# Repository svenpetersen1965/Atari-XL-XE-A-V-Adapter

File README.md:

# Atari-XL-XE-A-V-Adapter
This is an A/V-Adapter for the Atari 8bit XL and XE. It provides a connector for S-Video, which will work with the XE models and with XL models, that have the S-Video mod.

The BOM value (13.11.2023) for the PCB and components is 10.87€. This does not include the 3D printed case or any shipping fees to be paid for the components.

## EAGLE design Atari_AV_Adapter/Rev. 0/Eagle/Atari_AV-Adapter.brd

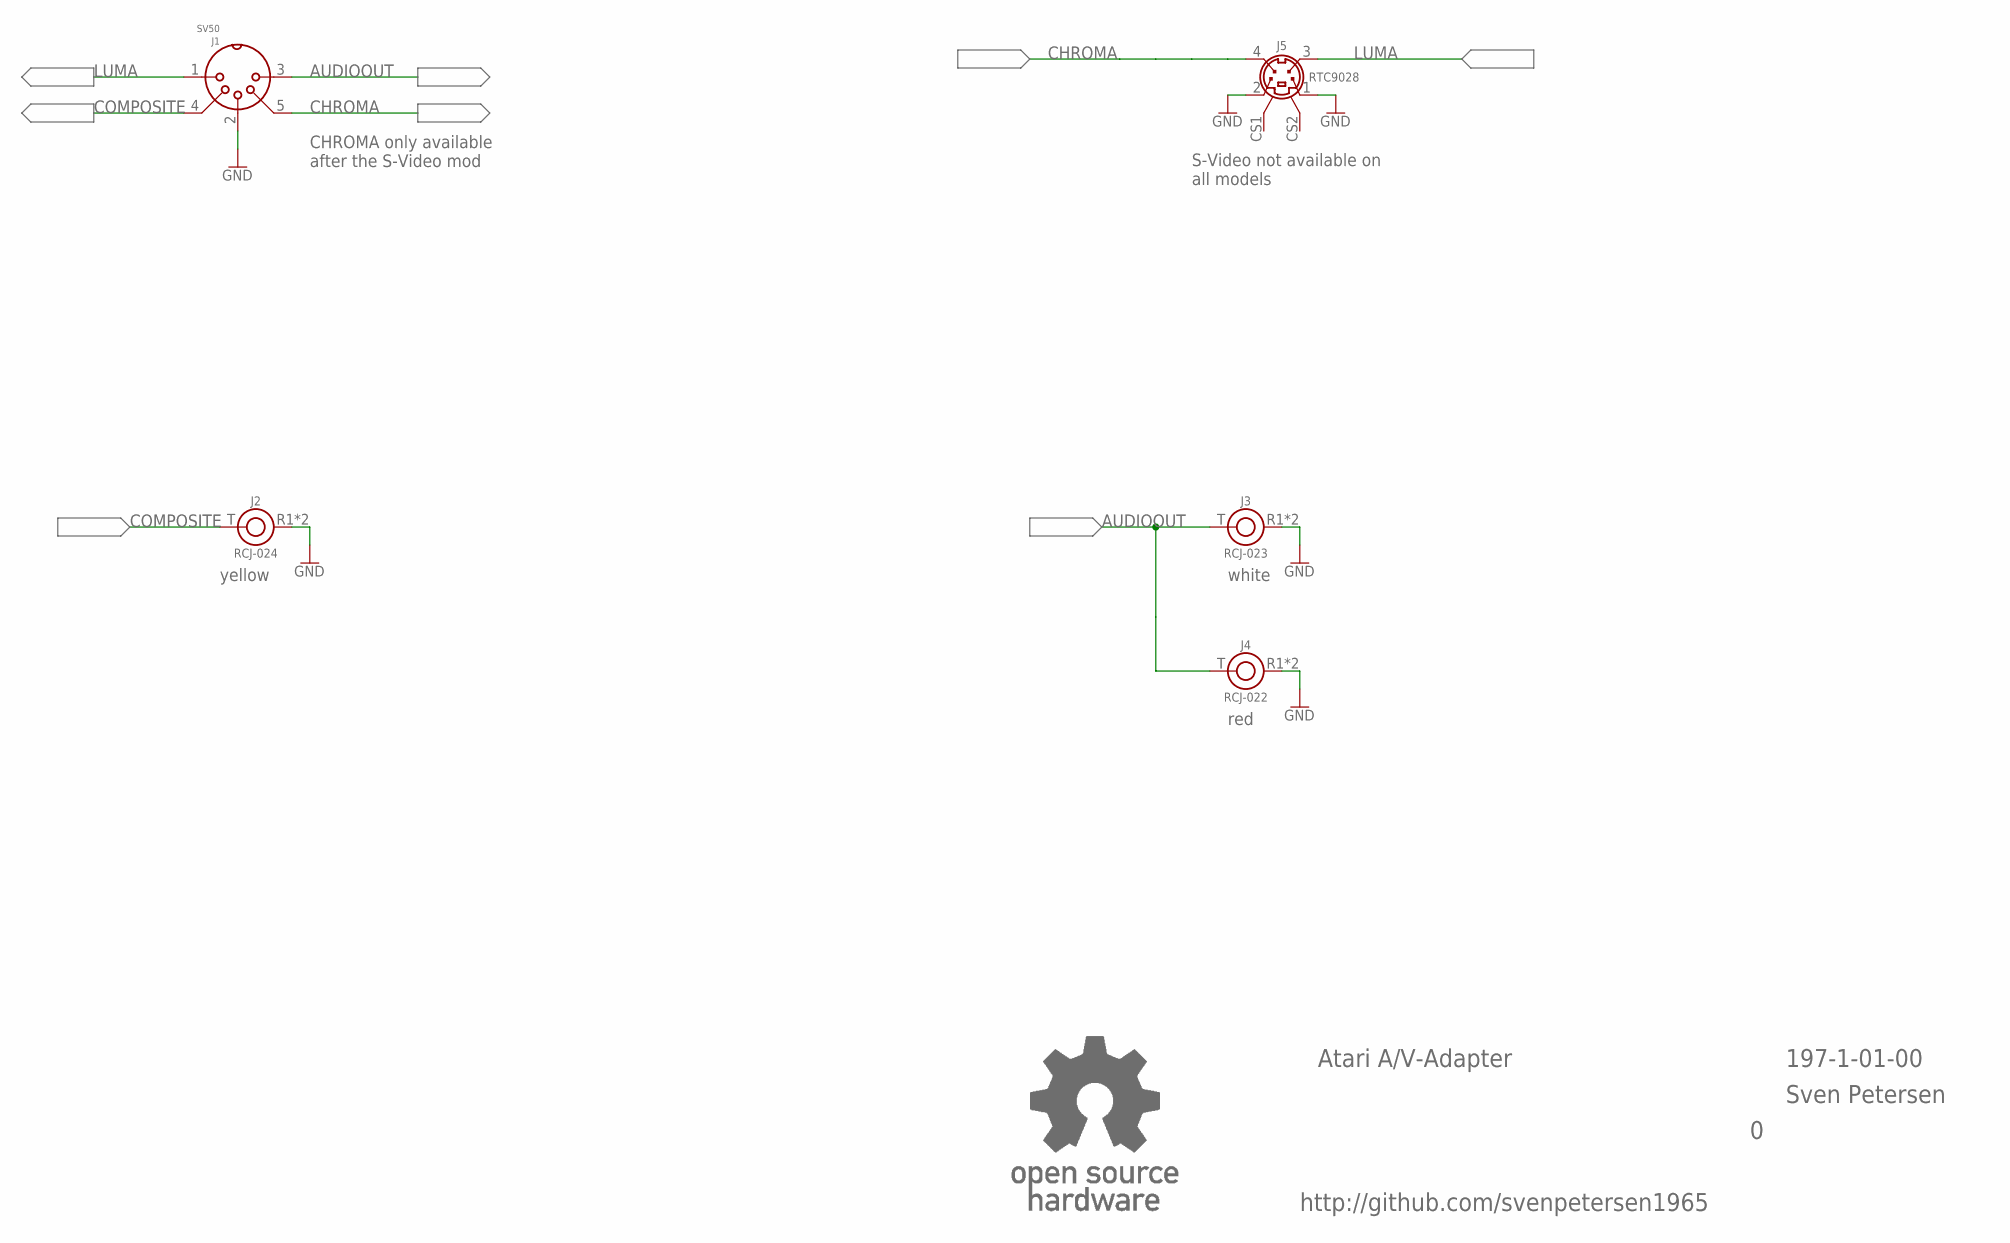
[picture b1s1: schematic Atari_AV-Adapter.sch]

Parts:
J1: SV50; SV50_INNER
J2: RCJ-024; RCJ-02X
J3: RCJ-023; RCJ-02X
J4: RCJ-022; RCJ-02X
J5: RTC9028; MINIDIN4_V
U$25: OPEN_SOURCE_HW; OPENHW

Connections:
AUDIOOUT: J1.3, J3.T, J4.T
CHROMA: J1.5, J5.4
COMPOSITE: J1.4, J2.T
GND: J1.2, J2.R1 (R), J2.R2 (R), J3.R1 (R), J3.R2 (R), J4.R1 (R), J4.R2 (R), J5.1, J5.2
LUMA: J1.1, J5.3

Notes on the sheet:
Atari A/V-Adapter
197-1-01-00
Sven Petersen
http://github.com/svenpetersen1965
CHROMA only available after the S-Video mod
S-Video not available on all models
white
red
yellow

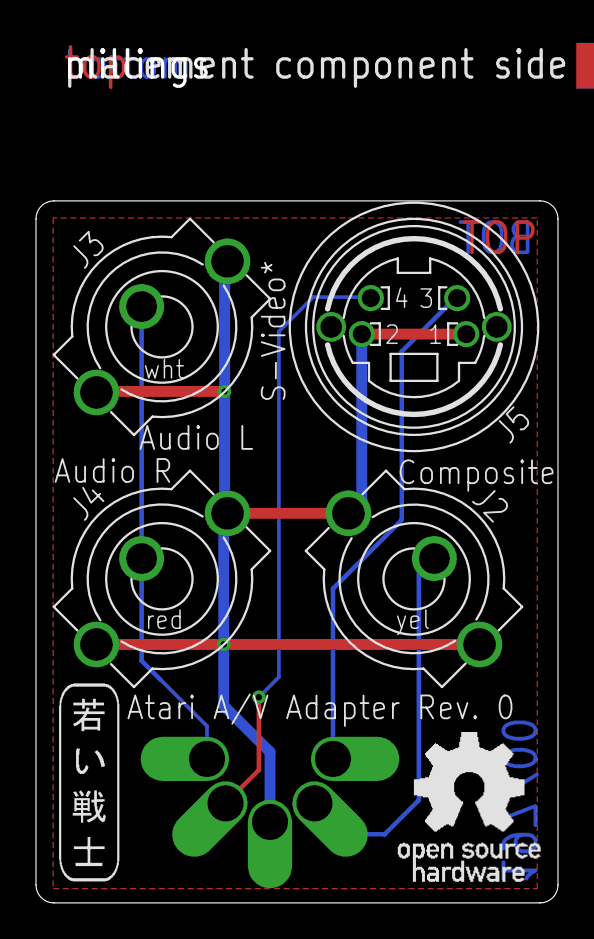
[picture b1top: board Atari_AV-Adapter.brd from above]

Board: 2 copper layers, 29.0 x 48.2 mm, 9 parts (1 on the bottom side), 5 nets.

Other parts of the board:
U$22: 2LAYER
U$23: SVEN_TAG
U$24: PCB-TITLE/

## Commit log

2023-05-28 Initial upload
2023-11-13 BOM value calculation
